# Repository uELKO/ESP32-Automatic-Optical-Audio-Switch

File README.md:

# Automatic Optical Audio Switch (ESP32)

Automatic switching between **two TOSLINK / SPDIF inputs** to **one output**
based on signal activity detection with an ESP32C3.

---

## Features
- 2× optical input → 1× optical output
- Automatic source selection (A/B)
- Signal detection via frequency measurement
- Configurable thresholds and timing
- Anti-flicker logic
- ESPHome firmware
- Web UI and Home Assistant integration
- No SPDIF decoding or audio processing
- USB-C powered
- 3D-printed enclosure

---

## Concept
Each optical input is converted into a digital pulse stream.
The ESP32 measures the divided SPDIF clock frequency and switches the output
to the active (playing) channel.

> [!NOTE]
> The actual audio path is switched purely in hardware. The ESP32 only controls the selection logic and does not touch the audio data stream itself.

---

## Build
1. Assemble PCB according to the KiCad project
2. Flash ESPHome/OTA firmware
3. Use Web UI or Home Assistant for configuration
4. Connect device to optical audio setup

---

## Documentation
Detailed explanations, diagrams and project logs are available on: **[Project page – Hackaday.io](https://hackaday.io/project/204791-automatic-optical-audio-switch-esp32)**

---

## PCBs
If you want to buy a bare or assembled PCB of this project, use this link to support me, thanks!

https://www.pcbway.com/project/shareproject/Automatic_Optical_Audio_Switch_ESP32_13712e76.html

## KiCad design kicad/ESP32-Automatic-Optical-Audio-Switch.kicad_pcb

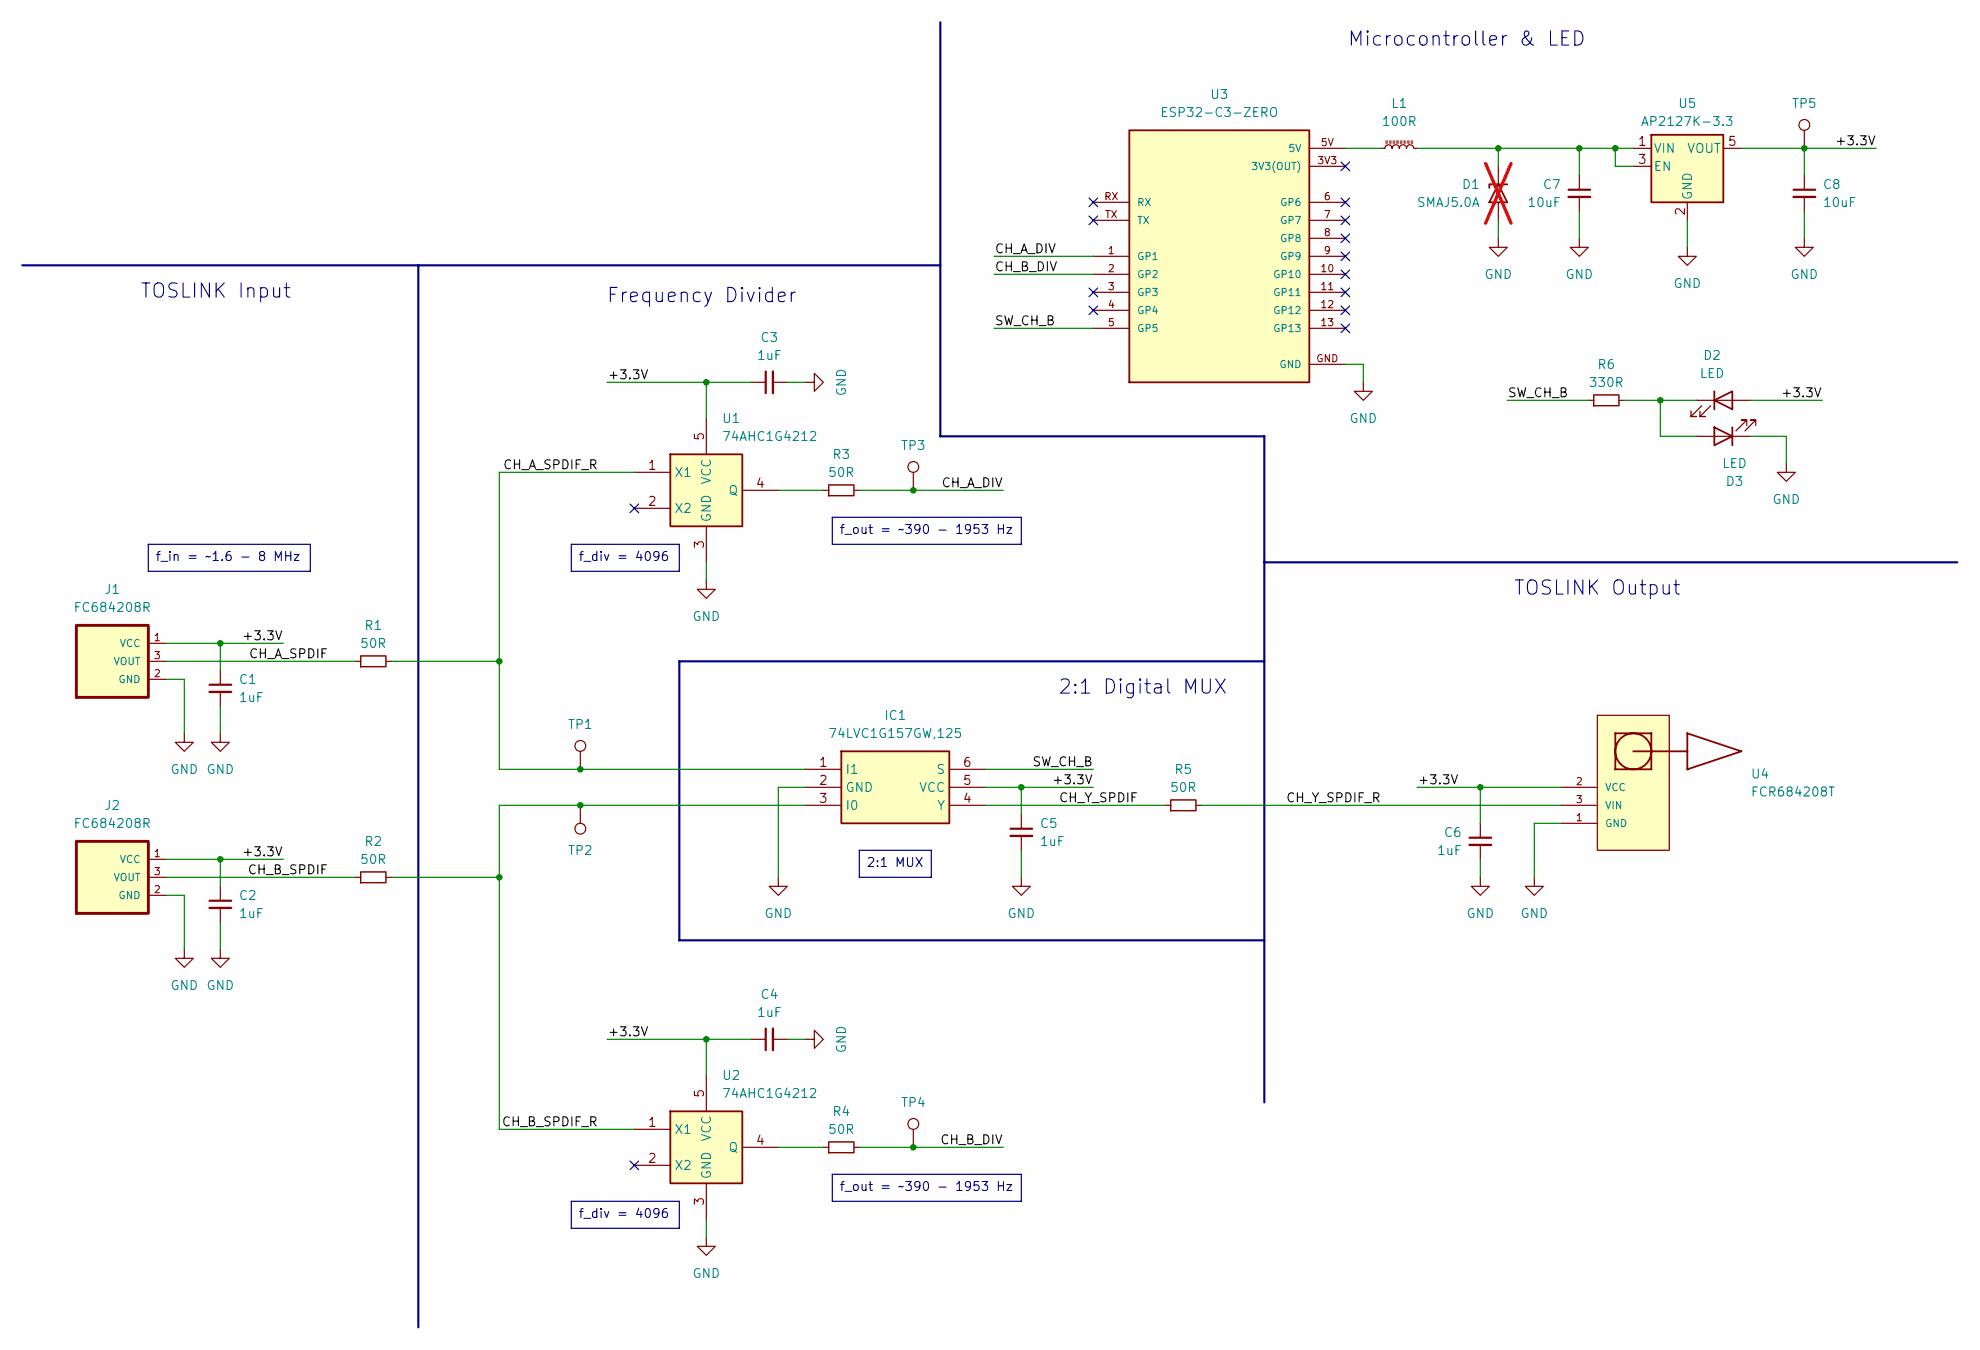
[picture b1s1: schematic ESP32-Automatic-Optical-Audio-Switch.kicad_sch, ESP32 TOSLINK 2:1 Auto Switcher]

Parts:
C1, C2, C3, C4, C5, C6: 1uF; C_0805_2012Metric
C7, C8: 10uF; C_0805_2012Metric
D1: SMAJ5.0A; D_SMA; not fitted
D2, D3: LED; LED_Kingbright_APA1606_1.6x0.6mm_Horizontal
IC1: 74LVC1G157GW,125; SOP65P210X110-6N; Mouser Part Number 771-74LVC1G157GW-G
J1, J2: FC684208R; ORJ-8
L1: 100R; L_0805_2012Metric
R1, R2, R3, R4, R5: 50R; R_0805_2012Metric
R6: 330R; R_0805_2012Metric
TP1, TP2, TP3, TP4, TP5: TestPoint; TestPoint_Pad_D1.0mm
U1, U2: 74AHC1G4212; SOT-353_SC-70-5
U3: ESP32-C3-ZERO; MODULE_ESP32-C3-ZERO; PARTREV NA
U4: FCR684208T; FCR684208T_R
U5: AP2127K-3.3; SOT-23-5

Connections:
/+3.3V: C1.1, C2.1, C3.1, C4.1, C5.1, C6.1, C8.1, D2.2 (A), IC1.5 (VCC), J1.1 (VCC), J2.1 (VCC), TP5.1, U1.5 (VCC), U2.5 (VCC), U4.2 (VCC), U5.5 (VOUT)
/CH_A_DIV: R3.2, TP3.1, U3.1 (GP1)
/CH_A_SPDIF: J1.3 (VOUT), R1.1
/CH_A_SPDIF_R: IC1.1 (I1), R1.2, TP1.1, U1.1 (X1)
/CH_B_DIV: R4.2, TP4.1, U3.2 (GP2)
/CH_B_SPDIF: J2.3 (VOUT), R2.1
/CH_B_SPDIF_R: IC1.3 (I0), R2.2, TP2.1, U2.1 (X1)
/CH_Y_SPDIF: IC1.4 (Y), R5.1
/CH_Y_SPDIF_R: R5.2, U4.3 (VIN)
/SW_CH_B: IC1.6 (S), R6.1, U3.5 (GP5)
GND: C1.2, C2.2, C3.2, C4.2, C5.2, C6.2, C7.2, C8.2, D1.2 (A2), D3.1 (K), IC1.2 (GND), J1.2 (GND), J2.2 (GND), U1.3 (GND), U2.3 (GND), U3.GND, U4.1 (GND), U4.MP1 (GND), U4.MP2 (GND), U5.2 (GND)
unnamed: D2.1 (K), D3.2 (A), R6.2
unnamed: L1.1, U3.5V
unnamed: R3.1, U1.4 (Q)
unnamed: R4.1, U2.4 (Q)
unnamed: C7.1, D1.1 (A1), L1.2, U5.1 (VIN), U5.3 (EN)

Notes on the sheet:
2:1 Digital MUX
Frequency Divider
TOSLINK Output
Microcontroller & LED
TOSLINK Input
f_div = 4096
f_out = ~390 - 1953 Hz
2:1 MUX
f_in = ~1.6 - 8 MHz

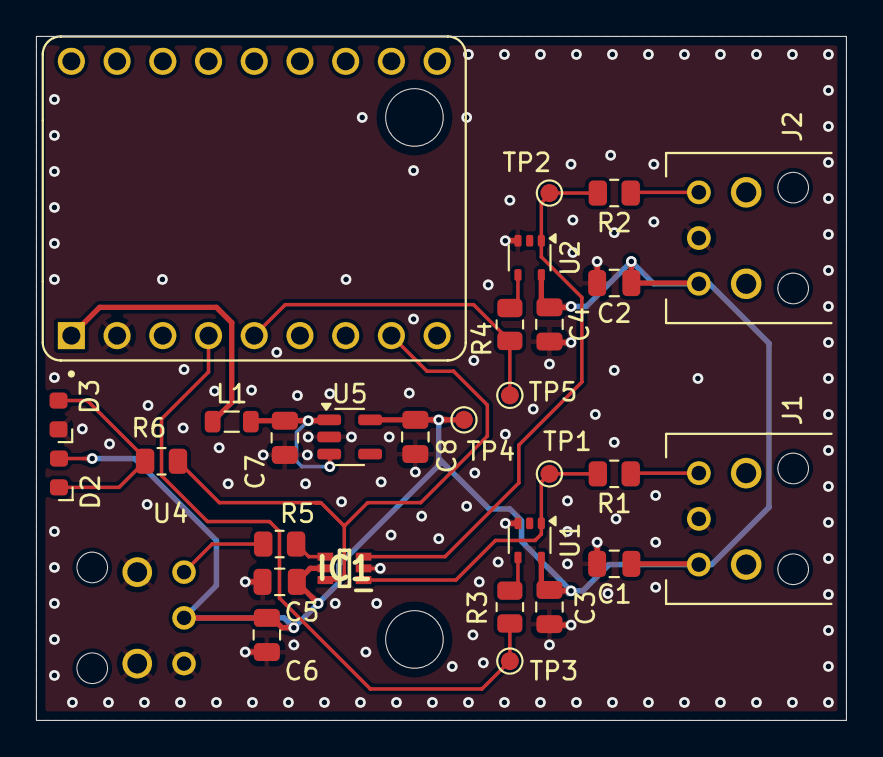
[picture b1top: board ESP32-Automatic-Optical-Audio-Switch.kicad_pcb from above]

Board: 2 copper layers, 45.0 x 38.0 mm, 30 parts (0 on the bottom side), 16 nets.

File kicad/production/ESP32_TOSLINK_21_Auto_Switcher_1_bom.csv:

Designator,Footprint,Quantity,Value,LCSC Part #
"C1, C2, C3, C4, C5, C6",0805,6,1uF,
"C7, C8",0805,2,10uF,
"D2, D3",LED_Kingbright_APA1606_1.6x0.6mm_Horizontal,2,LED,
IC1,SOP65P210X110-6N,1,"74LVC1G157GW,125",
"J1, J2",ORJ-8,2,FC684208R,
L1,0805,1,100R,
"R1, R2, R3, R4, R5",0805,5,50R,
R6,0805,1,330R,
"TP1, TP2, TP3, TP4, TP5",TestPoint_Pad_D1.0mm,5,TestPoint,
"U1, U2",SOT-353_SC-70-5,2,74AHC1G4212,
U3,MODULE_ESP32-C3-ZERO,1,ESP32-C3-ZERO,
U4,FCR684208T_R,1,FCR684208T,
U5,SOT-23-5,1,AP2127K-3.3,

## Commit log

2025-12-28 Enhance README with project details and features
    Expanded the README with detailed project information, features, and usage instructions.
2025-12-28 Add ESP32 optical audio switch KiCad and STEP files
    Initial commit of the ESP32-Automatic-Optical-Audio-Switch project, including KiCad PCB, schematic, project, and related files, as well as mechanical STEP models for enclosure parts.
2025-12-28 moved directory
2025-12-28 Clarify re-arming process in README
    Add detail about system re-arming after signal drop.
2026-01-02 Update image dimensions and add new images
2026-01-02 Add system diagram and update PCB for ESP32 switch
    Added a Draw.io system diagram for the ESP32 Optical Audio Switch. Updated the KiCad PCB and schematic files to reference the correct sheet file and replaced a capacitor footprint with the ESP32-C3-Z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
2026-01-02 Update README to remove WIP note
    Removed work in progress note from README.
2026-01-02 Revise README for Automatic Optical Audio Switch
    Updated project overview and features for clarity and conciseness. Added build instructions and improved formatting.
2026-01-02 Remove DIY smart-home audio integration line
2026-01-02 Revise README for clarity and add documentation section
2026-01-02 Update Hackaday.io project link in README
2026-01-06 Add PCB purchasing information to README
    Added section about purchasing PCBs for the project.
2026-01-06 Fix URL formatting in README.md
2026-01-06 Added production files
